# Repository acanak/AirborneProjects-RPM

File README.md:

# AirborneProjects-RPM
Repository with the Arduino Nano source files to create an RPM counter of up to 8 motors simultaneously.

It also contains the Eagle files, board and schematics, of the sensors and schmitt triggers that act as a shield to the Arduino Nano.

In the contrib/ardupilot submodule is a fork to a ardupilot repository which contains the implementation of the sensors for the Ardupilot code, including integration with SerialManager, Logger and new Mavlink messages.

Airborne Projects is a company and is not actively developing this product but if there is interest in further development let us know.

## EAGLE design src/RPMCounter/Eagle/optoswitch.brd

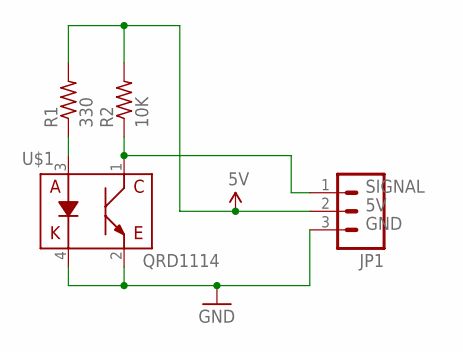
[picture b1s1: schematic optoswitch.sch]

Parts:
JP1: M03POLAR; MOLEX-1X3
R1: 330; R2512
R2: 10K; R2512
U$1: QRD1114

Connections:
5V: JP1.2, R1.2, R2.2
GND: JP1.3, U$1.2 (C), U$1.4 (K)
unnamed: R1.1, U$1.3 (A)
SIGNAL: JP1.1, R2.1, U$1.1 (E)

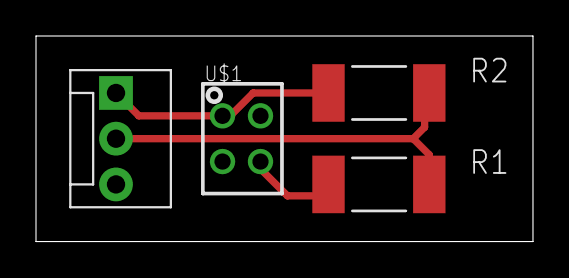
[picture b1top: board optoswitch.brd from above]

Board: 2 copper layers, 27.6 x 11.4 mm, 4 parts (0 on the bottom side), 4 nets.

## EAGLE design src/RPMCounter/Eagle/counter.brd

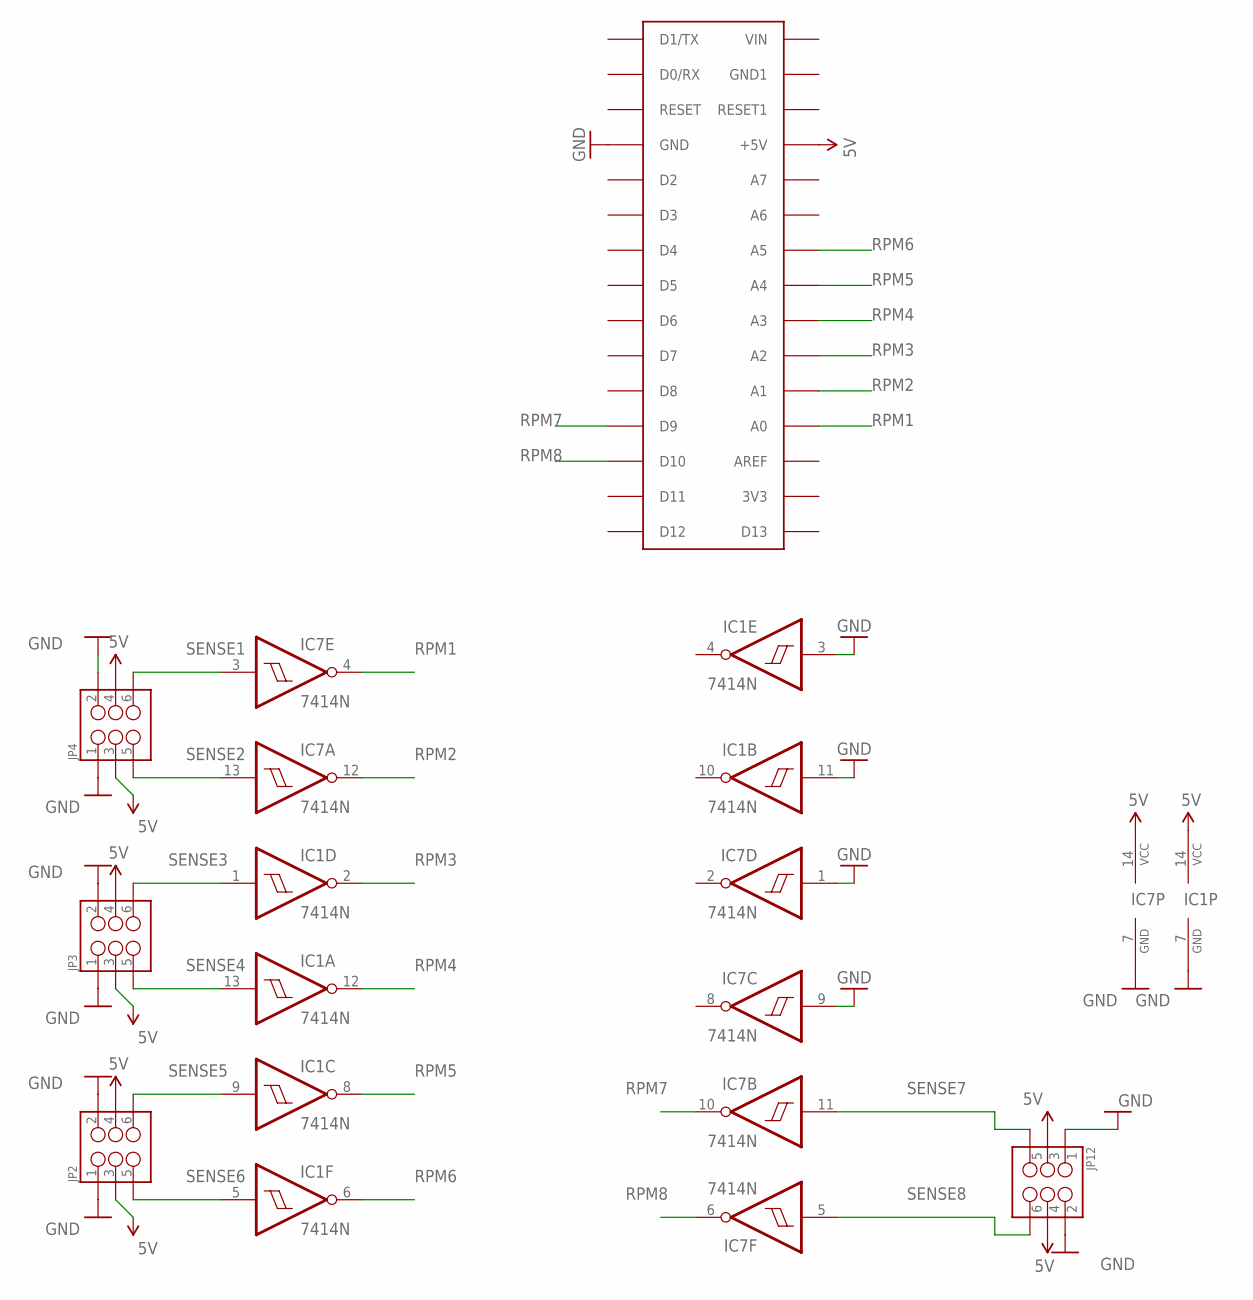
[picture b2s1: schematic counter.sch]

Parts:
IC1, IC7: 7414N; DIL14
JP2, JP3, JP4, JP12: M03X2NO_SILK; 2X3-NS
U$1: ARDUINONANO; PDIP-32

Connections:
5V: IC1.14 (VCC), IC7.14 (VCC), JP2.3, JP2.4, JP3.3, JP3.4, JP4.3, JP4.4, JP12.3, JP12.4, U$1.+5V
GND: IC1.3 (I), IC1.7 (GND), IC1.11 (I), IC7.1 (I), IC7.7 (GND), IC7.9 (I), JP2.1, JP2.2, JP3.1, JP3.2, JP4.1, JP4.2, JP12.1, JP12.2, U$1.GND
RPM1: IC7.4 (O), U$1.A0
RPM2: IC7.12 (O), U$1.A1
RPM3: IC1.2 (O), U$1.A2
RPM4: IC1.12 (O), U$1.A3
RPM5: IC1.8 (O), U$1.A4
RPM6: IC1.6 (O), U$1.A5
RPM7: IC7.10 (O), U$1.D9
RPM8: IC7.6 (O), U$1.D10
SENSE1: IC7.3 (I), JP4.6
SENSE2: IC7.13 (I), JP4.5
SENSE3: IC1.1 (I), JP3.6
SENSE4: IC1.13 (I), JP3.5
SENSE5: IC1.9 (I), JP2.6
SENSE6: IC1.5 (I), JP2.5
SENSE7: IC7.11 (I), JP12.5
SENSE8: IC7.5 (I), JP12.6

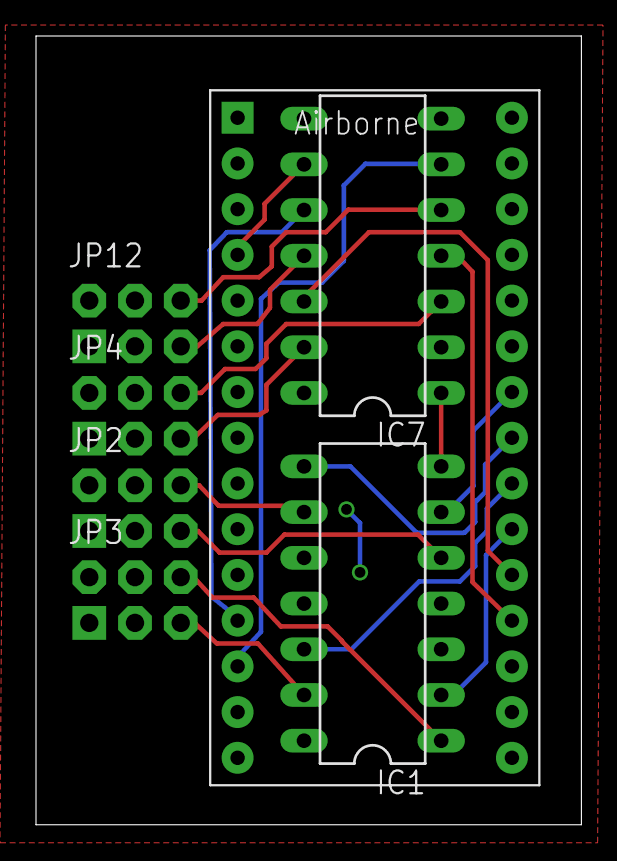
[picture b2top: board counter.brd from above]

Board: 2 copper layers, 30.3 x 43.8 mm, 7 parts (0 on the bottom side), 18 nets.

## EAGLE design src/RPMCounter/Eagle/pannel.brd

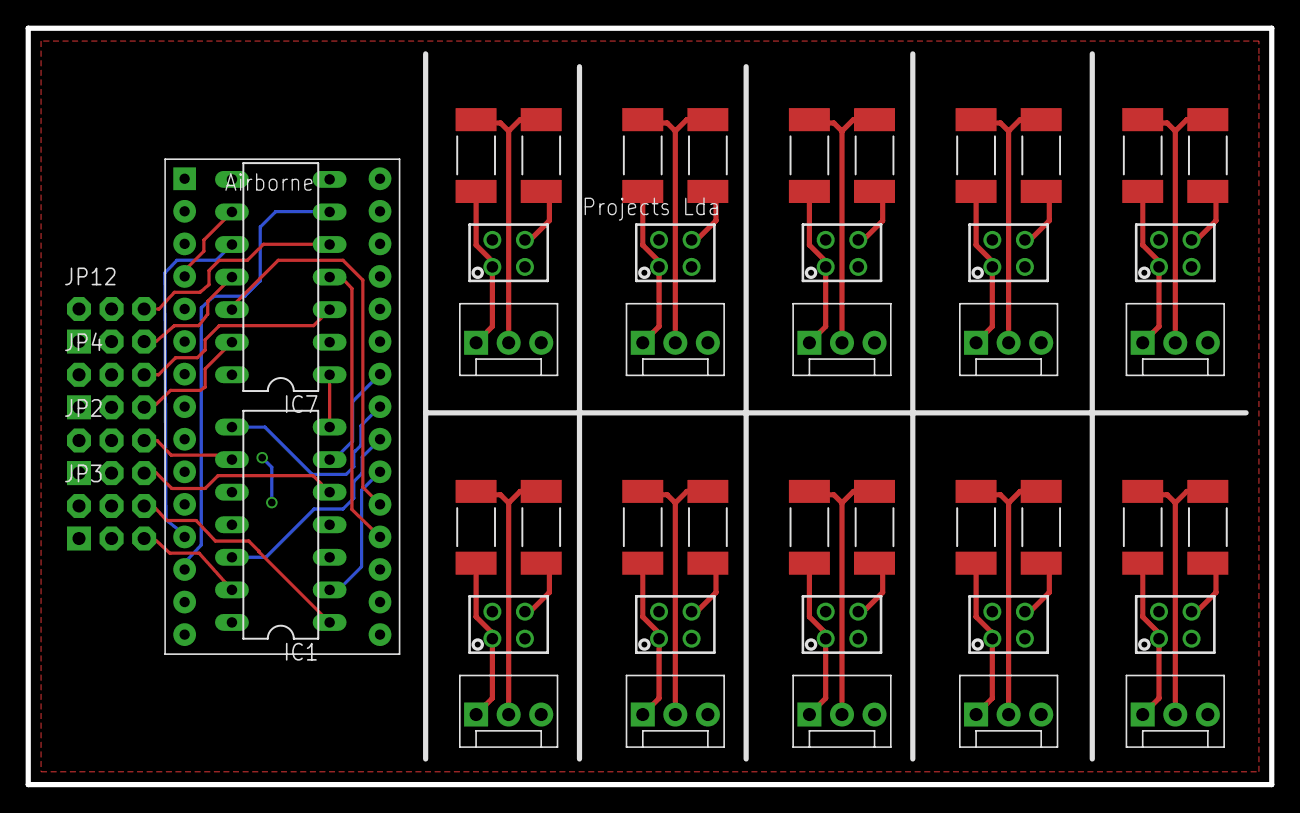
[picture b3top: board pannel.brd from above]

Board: 2 copper layers, 97.0 x 59.0 mm, 47 parts (0 on the bottom side), 38 nets.

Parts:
IC1, IC7: 7414N; DIL14
JP1, JP5, JP6, JP7, JP8, JP9, JP10, JP11, JP13, JP14: MOLEX-1X3
JP2, JP3, JP4, JP12: 2X3-NS
R1, R3, R5, R7, R9, R11, R13, R15, R17, R19: 330; R2512
R2, R4, R6, R8, R10, R12, R14, R16, R18, R20: 10K; R2512
U$1, U$3, U$4, U$5, U$6, U$7, U$8, U$9, U$10, U$11: QRD1114
U$2: ARDUINONANO; PDIP-32

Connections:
5V: IC1.14, IC7.14, JP1.2, JP2.3, JP2.4, JP3.3, JP3.4, JP4.3, JP4.4, JP5.2, JP6.2, JP7.2, JP8.2, JP9.2, JP10.2, JP11.2, JP12.3, JP12.4, JP13.2, JP14.2, R1.2, R2.2, R3.2, R4.2, R5.2, R6.2, R7.2, R8.2, R9.2, R10.2, R11.2, R12.2, R13.2, R14.2, R15.2, R16.2, R17.2, R18.2, R19.2, R20.2, U$2.+5V
GND: IC1.3, IC1.7, IC1.11, IC7.1, IC7.7, IC7.9, JP1.3, JP2.1, JP2.2, JP3.1, JP3.2, JP4.1, JP4.2, JP5.3, JP6.3, JP7.3, JP8.3, JP9.3, JP10.3, JP11.3, JP12.1, JP12.2, JP13.3, JP14.3, U$1.2, U$1.4, U$2.GND, U$3.2, U$3.4, U$4.2, U$4.4, U$5.2, U$5.4, U$6.2, U$6.4, U$7.2, U$7.4, U$8.2, U$8.4, U$9.2, U$9.4, U$10.2, U$10.4, U$11.2, U$11.4
unnamed: R1.1, U$1.3
unnamed: R3.1, U$3.3
unnamed: R5.1, U$4.3
unnamed: R7.1, U$5.3
unnamed: R9.1, U$6.3
unnamed: R11.1, U$7.3
unnamed: R13.1, U$8.3
unnamed: R15.1, U$9.3
unnamed: R17.1, U$10.3
unnamed: R19.1, U$11.3
RPM1: IC7.4, U$2.A0
RPM2: IC7.12, U$2.A1
RPM3: IC1.2, U$2.A2
RPM4: IC1.12, U$2.A3
RPM5: IC1.8, U$2.A4
RPM6: IC1.6, U$2.A5
RPM7: IC7.10, U$2.D9
RPM8: IC7.6, U$2.D10
SENSE1: IC7.3, JP4.6
SENSE2: IC7.13, JP4.5
SENSE3: IC1.1, JP3.6
SENSE4: IC1.13, JP3.5
SENSE5: IC1.9, JP2.6
SENSE6: IC1.5, JP2.5
SENSE7: IC7.11, JP12.5
SENSE8: IC7.5, JP12.6
SIGNAL: JP1.1, R2.1, U$1.1
SIGNAL1: JP5.1, R4.1, U$3.1
SIGNAL2: JP6.1, R6.1, U$4.1
SIGNAL3: JP7.1, R8.1, U$5.1
SIGNAL4: JP8.1, R10.1, U$6.1
SIGNAL5: JP9.1, R12.1, U$7.1
SIGNAL6: JP10.1, R14.1, U$8.1
SIGNAL7: JP11.1, R16.1, U$9.1
SIGNAL8: JP13.1, R18.1, U$10.1
SIGNAL9: JP14.1, R20.1, U$11.1

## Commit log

2016-02-09 Software and Hardware files for a RPM counter compatible with Ardupilot.
2016-02-09 Modified README with some information about the repository.

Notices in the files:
parts and their libraries:
SparkFun-Connectors: Licensing: Creative Commons ShareAlike 4.0 International - https://creativecommons.org/licenses/by-sa/4.0
